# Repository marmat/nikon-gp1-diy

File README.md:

DIY GPS Module for Nikon DSLRs
==============================

Using a GPS Module, most modern Nikon DSLRs are able to automatically geotag
pictures right when taking them. Unfortunately, the official Nikon GP-1 is very
expensive (~200€). This project contains all necessary information to create a
low-cost module which works just as well. This DIY version costs around 30€
(40$).

- [Requirements](#requirements)
  - [Tools](#tools)
  - [Parts](#parts)
  - [Electronic Components](#electronic-components)
- [Building Instructions](#building-instructions)
- [Technical Details](#technical-details)
  - [Nikon GPS Port Specs](#nikon-gps-port-specs)
  - [Protocol](#protocol)
  - [Schematics](#schematics)
- [Images](#images)
- [Sources](#sources)

See also the [Building Log](BUILD.md).

Requirements
------------

### Tools

- Soldering Equipment
- Sharp knife to cut soft plastic
- A small dremel or similar to cut hard plastic
- Plastic Glue
- Screwdriver

### Parts

| Item              | Description                                              |
| ----------------- | -------------------------------------------------------- |
| Case              | Hammond 1551NBK                                          |
| PCB               | Board layout available in [eagle](eagle/) folder. Either create your own if you have the equipment, visit your local [FabLab](http://en.wikipedia.org/wiki/Fablab) or let the PCB be created professionally (look for cheap companies in your region). |
| Cable & Connector | Can be taken from a cheap remote cable trigger.          |

### Electronic Components

|  ID |  Item description |     Part No.    |  Size |
| --- | ----------------- | --------------- | ----- |
| IC1 | GPS Module        | Maestro A2235-H |       |
| IC2 | Voltage Regulator | LP2985-33       | SOT23 |
| IC3 | Level Shifter     | MAX3370         | 5SC70 |
| R1  | Resistor          | 10 kOhm         | 1206  |
| R2  | Resistor          | 2.2 kOhm        | 1206  |
| R3  | Resistor          | 2.2 kOhm        | 1206  |
| C1  | Capacitor         | 10 nF           | 0805  |
| C2  | Capacitor         | 1 µF            | 0805  |
| C3  | Capacitor         | 2.2 µF          | 0805  |

Building Instructions
---------------------

1. Disassemble the remote trigger. If the cable has only 3 wires, you will have
   to cut the connector in half and rewire them to pins 3, 4 and 7. Use plastic
   glue and a vice to put the two connector halves back together after rewiring.
   Before rewiring, you can optionally shorten the cable to your desired length.
   Make sure to preserve the cable protection on the side of the trigger. We
   will reuse it for our GPS module.
2. Solder all electronic components onto the the PCB. I have done this in the
   order from largest to smallest, but do whatever is most comfortable to you.
   You might also want to consider reflow soldering, especially for the GPS
   module. If you do regular soldering, feel free to keep the ground pads on the
   bottom of the GPS module unconnected. I have done so and it does not cause
   any issues.
3. (optional, recommended) Do an electrical check of the PCB using a Multimeter.
   Make sure no pads are connected that shouldn't be connected.
4. (optional) Attach a 5V power source to the board (pads P1 and P3). Attach an
   oscilloscope to P2. You should see a burst of data coming in at about 1Hz,
   otherwise the pin should have a high level (+5V).
5. The PCB will be placed inside the lid of the case. Optional: use glue to
   attach the PCB permanently.
6. Use a dremel to cut a slot into the case with the width of the cable. Check
   if the original cable protection fits into the slot and adjust if necessary.
7. Shorten the part of the cable which will be inside the case and solder the
   wires to pads P1-P3.
8. Assemble the case by using the supplied case screws.
9. Go outside and check if the device operates properly. **Note:** it might take
   a while for the first GPS fix. Make sure to have a good visibility to the
   sky.
10. (optional) Use plastic glue to attach a hot shoe protection cap to the lid
    of the case (such that the GPS antenna will face upward). This will allow
    for a secure mounting of the device on the camera.

Technical Details
-----------------

### Nikon GPS Port Specs

* Proprietary 8-pin connector,
  [pinout](http://pinoutsguide.com/DigitalCameras/nikon_d90_pinout.shtml)
* Operating voltage: 5V

### Protocol

The camera awaits NMEA-compliant messages over the GPS DATA pin. Data is
transmitted via UART with 4800 baud, no parity, 1 stop bit.

### Schematics

The schematics and PCB layout was created using Eagle. You can find all required
files in the [eagle](eagle/) subdirectory. Additionally, the folder
[eagle-lbr](eagle-lbr/) contains a library of custom made components which are
not part of the original Eagle libraries. Since the camera accepts raw NMEA
data, the circuit is extremely simple and does not require additional
controllers. The only difficulty is based in the operating voltage: the camera
uses 5V while the GPS module operates with 3.3V. Therefore a voltage regulator
and level shifter has been added to ensure correct levels on both sides.

Images
------

Sources
-------

1. [Peter Miller Photography](http://www.petermillerphoto.com/nikongps/nikongps2.html)
2. [Homepage of Bálint Kis](http://www.k-i-s.org/index.php?item=13)
3. [Pinouts Guide](http://pinoutsguide.com/DigitalCameras/nikon_d90_pinout.shtml)

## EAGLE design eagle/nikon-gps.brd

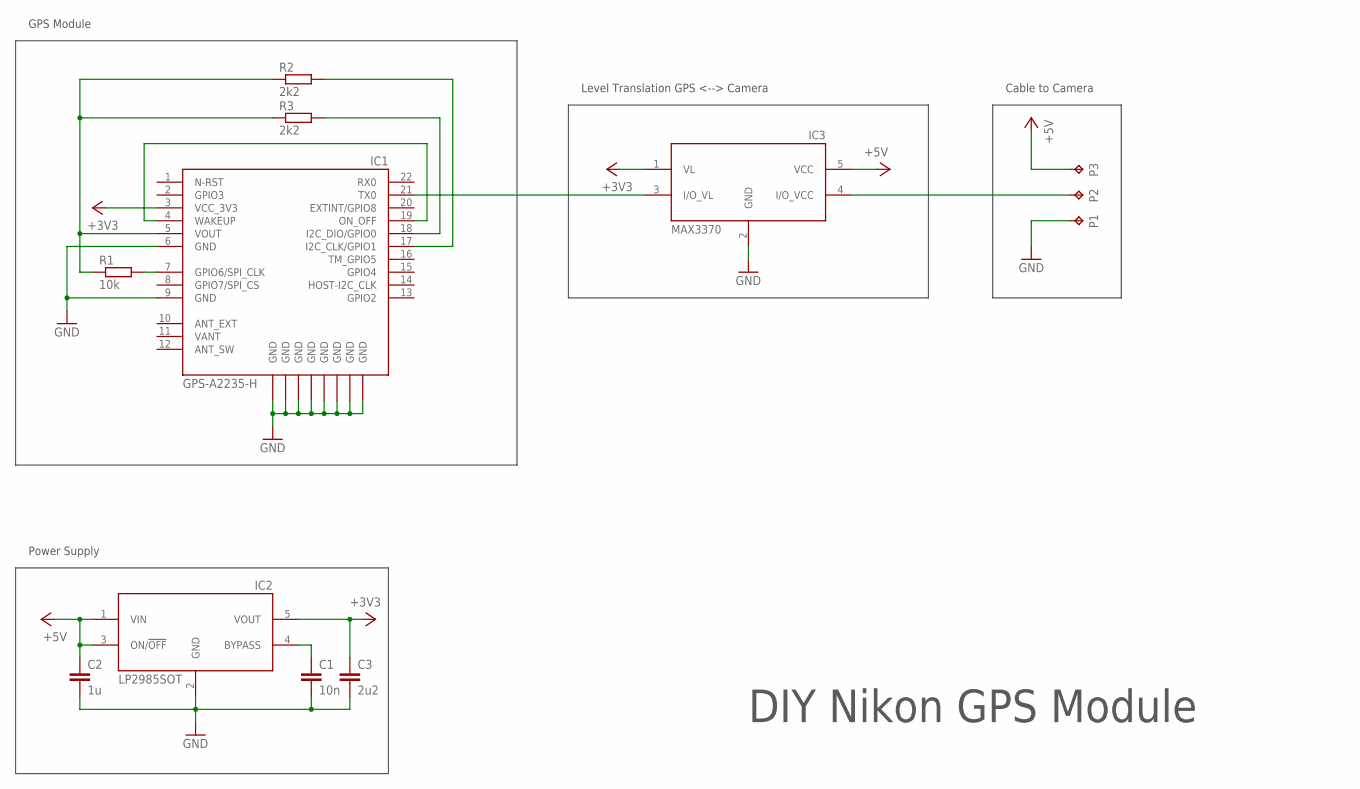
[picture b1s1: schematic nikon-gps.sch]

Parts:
C1: 10n; C0805
C2: 1u; C0805
C3: 2u2; C0805
IC1: GPS-A2235-H
IC2: LP2985SOT; SOT23-5L
IC3: MAX3370; SC70-5L
P1, P2, P3: TPTP12SQ; TP12SQ
R1: 10k; M1206
R2, R3: 2k2; M1206

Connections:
+3V3: C3.1, IC1.3 (VCC_3V3), IC2.5 (VOUT), IC3.1 (VL)
+5V: C2.1, IC2.1 (VIN), IC2.3 (ON/!OFF), IC3.5 (VCC), P3.TP
GND: C1.2, C2.2, C3.2, IC1.6 (GND), IC1.9 (GND), IC1.GND_PAD@1 (GND), IC1.GND_PAD@2 (GND), IC1.GND_PAD@3 (GND), IC1.GND_PAD@4 (GND), IC1.GND_PAD@5 (GND), IC1.GND_PAD@6 (GND), IC1.GND_PAD@7 (GND), IC1.GND_PAD@8 (GND), IC2.2 (GND), IC3.2 (GND), P1.TP
unnamed: C1.1, IC2.4 (BYPASS)
unnamed: IC1.21 (TX0), IC3.3 (I/O_VL)
unnamed: IC3.4 (I/O_VCC), P2.TP
unnamed: IC1.7 (GPIO6/SPI_CLK), R1.2
unnamed: IC1.18 (I2C_DIO/GPIO0), R3.2
unnamed: IC1.17 (I2C_CLK/GPIO1), R2.2
unnamed: IC1.4 (WAKEUP), IC1.19 (ON_OFF)
VANT: IC1.11 (VANT)
VOUT: IC1.5 (VOUT), R1.1, R2.1, R3.1

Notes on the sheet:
DIY Nikon GPS Module
Power Supply
Cable to Camera
Level Translation GPS <--> Camera
GPS Module

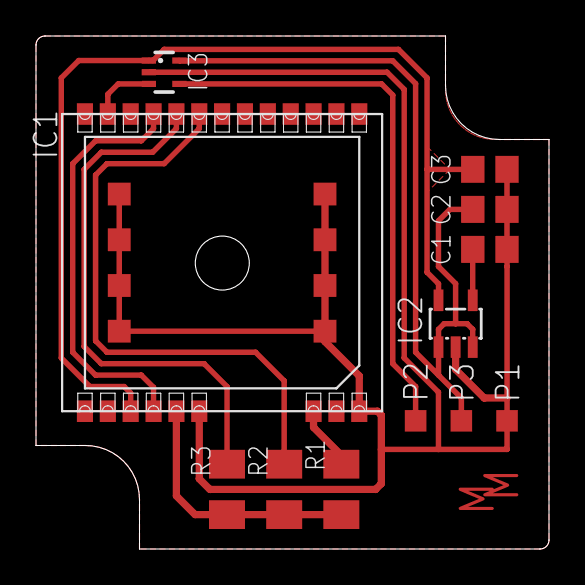
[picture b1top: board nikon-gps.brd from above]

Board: 2 copper layers, 28.5 x 28.5 mm, 12 parts (0 on the bottom side), 11 nets.

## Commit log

2014-05-10 Initial commit.
2014-05-11 Adding rough part list. Fixing some typo. Adding empty eagle project.
2014-05-11 Adding my personal EAGLE library with selfmade packages.
2014-05-11 Adding A2235-H device, symbol & package to selfmade lib.
    Updating partlist according to more recent A2235-H user manual
    recommendations.
2014-05-11 Removing machine-specific EAGLE project file.
    Adding plenty of ignorable EAGLE file types to gitignore.
2014-05-12 Updating part list with new findings. Adding paper prototype.
    Adding notes about switch placement and interior dimensions
    of 1551NBK.
2014-05-12 Adding PTS645V device + package + symbol to selfmade library.
2014-05-13 Adding variant of the paper prototype.
2014-05-13 Update: switch not needed according to latest user manual of A2235H.
    Adding MAX3370 to selfmade library.
2014-05-13 Adding initial schematics and board layout.
2014-05-14 First stab at a PCB layout.
    The part placement might still be optimized, esp. if we consider adding
    a Status-LED.
2014-05-15 Adding missing capacitors for LP2985 voltage regulator.
2014-05-16 Updating README to reflect current project status.
2014-05-16 Updating Partlist to match Schematics.
    Updating most of the prices to match Mouser price + 19% VAT.
    Adding note regarding remote trigger.
2014-05-16 Slightly adjusting placement of cable soldering pads.
2014-05-17 Adding PDFs of PCB and Schematic for easier preview on GitHub.
2014-05-20 Adding more info on casing.
2014-05-20 Updating PCB to fit inside the lid (now 28.5mm x 28.5mm).
2014-05-26 Creating files for PCB mill as per hci.rwth-aachen.de/mill instructions.
2014-05-26 Updating pdf preview of board layout.
2014-05-27 Project update.
2014-05-29 Reducing file size of images. Moving them into separate folder.
2014-05-29 Project finished. Cleaning up README and adding building instructions.
2018-12-15 Fix typo in parts list.
